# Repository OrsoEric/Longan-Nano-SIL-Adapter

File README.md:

# Longan-Nano-SIL-Adapter
SIL Adapter for the Longan Nano evaluation board for the GD32VF103. Allows vertical mounting for the board. Includes RS485 communication with 3.5mm Audio Jacks.

**Connector Pinout**  

**Schematics**  

**Routing**  

**Gerber**  

**BOM**
*Part* 	*Value*  
CB-COM-1 	1u  
CF-COM-1 	100n  
CF-COM-2 	100n  
CON-COM-1 	JACK_SMD_3MM5  
CON-COM-2 	JACK_SMD_3MM5  
CON-UC-1 	2X2.54mm Male  
CON-UC-2 	8X2.54mm Male  
CON-UC-3 	8X2.54mm Male  
CP-UC-1 	100u  
IC-COM-1 	SN75176  
IC-UC-1 	LONGAN-NANO  
LF1-COM-1 	BEAD 500mA  
RD-COM-1 	720  
RS-COM-2 	10  
RS-COM-3 	10  
RS-UC-1 	4X1K  
RT-COM-1 	120  
RU-COM-1 	720

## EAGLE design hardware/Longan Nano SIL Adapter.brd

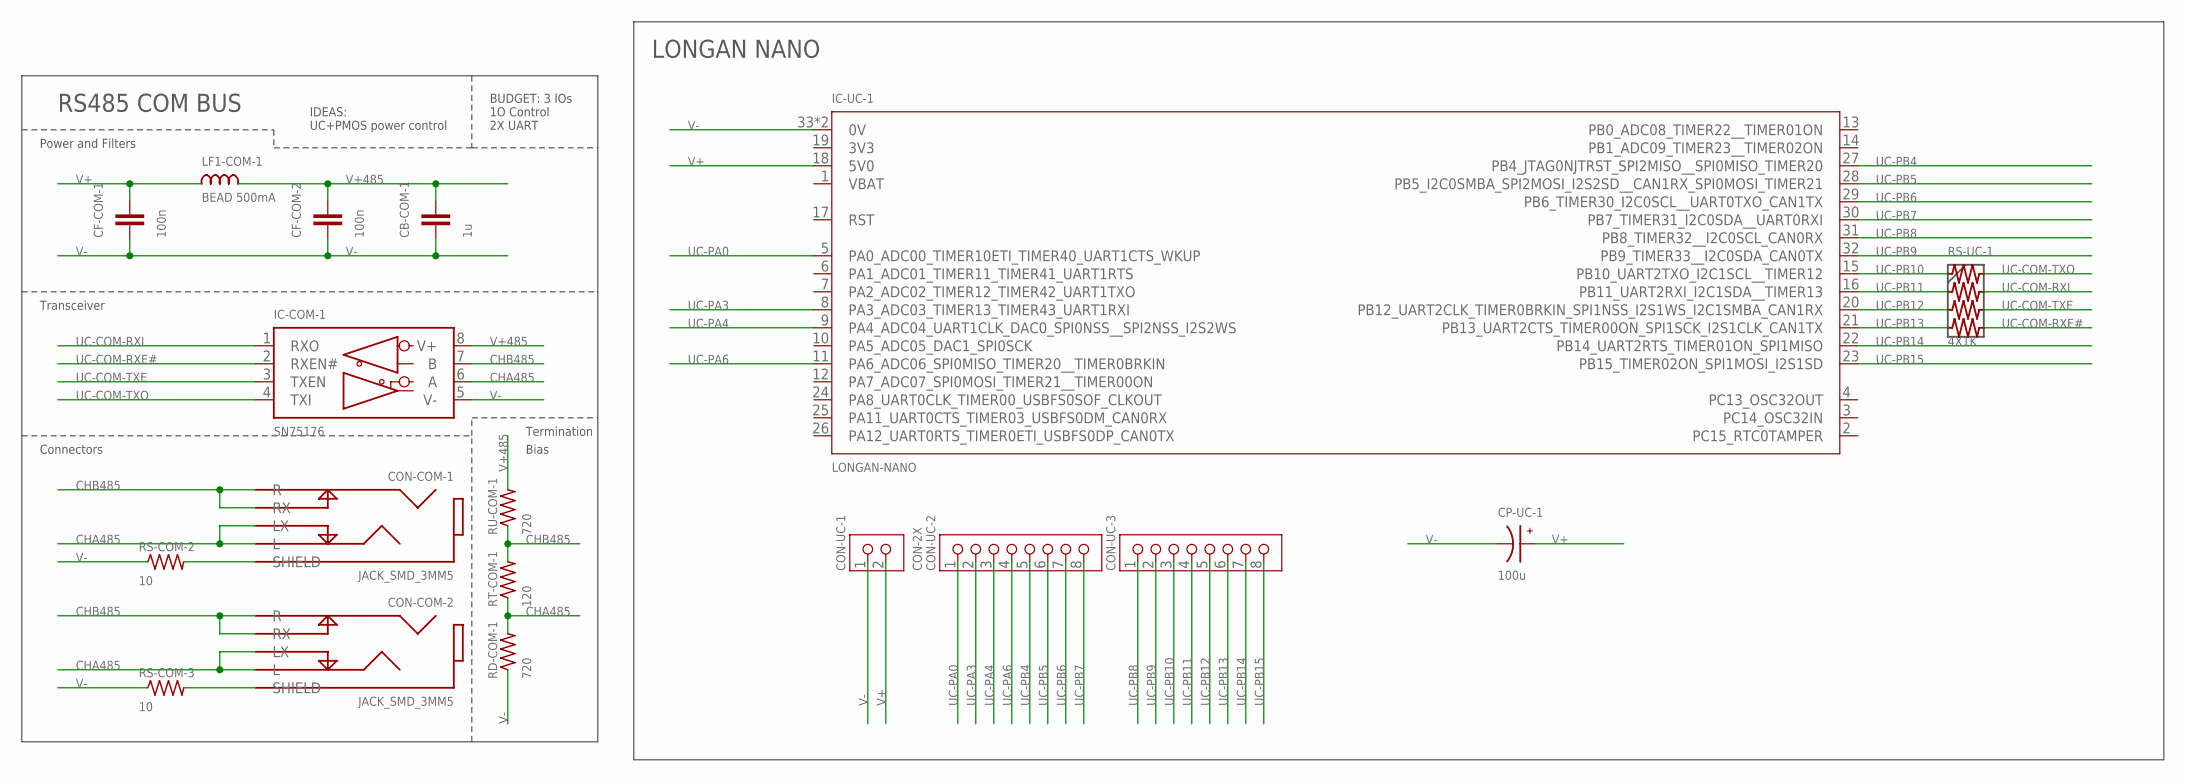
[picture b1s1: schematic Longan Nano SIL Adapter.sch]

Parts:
CB-COM-1: 1u; SMD-M2012
CF-COM-1, CF-COM-2: 100n; SMD-M2012
CON-COM-1, CON-COM-2: JACK_SMD_3MM5
CON-UC-1: CON-2X; TH-2X2.54
CON-UC-2, CON-UC-3: CON-8X; TH-8X2.54
CP-UC-1: 100u; TH-BARREL-2M54-6M0
IC-COM-1: SN75176; DIL08
IC-UC-1: LONGAN-NANO
LF1-COM-1: BEAD 500mA; SMD-M2012
RD-COM-1: 720; SMD-M2012
RS-COM-2, RS-COM-3: 10; SMD-M2012
RS-UC-1: 4X1K; SMD-M2012-X4
RT-COM-1: 120; TH-LINE-2M54-3M0
RU-COM-1: 720; SMD-M2012

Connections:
3V3: IC-UC-1.19 (3V3)
CHA485: CON-COM-1.L, CON-COM-1.LX, CON-COM-2.L, CON-COM-2.LX, IC-COM-1.6 (A), RD-COM-1.2, RT-COM-1.P$1 (1)
CHB485: CON-COM-1.R, CON-COM-1.RX, CON-COM-2.R, CON-COM-2.RX, IC-COM-1.7 (B), RT-COM-1.P$2 (2), RU-COM-1.1
unnamed: CON-COM-1.SHIELD, RS-COM-2.2
unnamed: CON-COM-2.SHIELD, RS-COM-3.2
UC-COM-RXE#: IC-COM-1.2 (RXEN#), RS-UC-1.4B
UC-COM-RXI: IC-COM-1.1 (RXO), RS-UC-1.2B
UC-COM-TXE: IC-COM-1.3 (TXEN), RS-UC-1.3B
UC-COM-TXO: IC-COM-1.4 (TXI), RS-UC-1.1B
UC-PA0: CON-UC-2.1, IC-UC-1.5 (PA0_ADC00_TIMER10ETI_TIMER40_UART1CTS_W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)
UC-PA3: CON-UC-2.2, IC-UC-1.8 (PA3_ADC03_TIMER13_TIMER43_UART1RXI)
UC-PA4: CON-UC-2.3, IC-UC-1.9 (PA4_ADC04_UART1CLK_DAC0_SPI0NSS__SPI2NS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)
UC-PA6: CON-UC-2.4, IC-UC-1.11 (PA6_ADC06_SPI0MISO_TIMER20__TIMER0BRKIN)
UC-PB4: CON-UC-2.5, IC-UC-1.27 (PB4_JTAG0NJTRST_SPI2MISO__SPI0MISO_TIME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)
UC-PB5: CON-UC-2.6, IC-UC-1.28 (PB5_I2C0SMBA_SPI2MOSI_I2S2SD__CAN1RX_SP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)
UC-PB6: CON-UC-2.7, IC-UC-1.29 (PB6_TIMER30_I2C0SCL__UART0TXO_CAN1TX)
UC-PB7: CON-UC-2.8, IC-UC-1.30 (PB7_TIMER31_I2C0SDA__UART0RXI)
UC-PB8: CON-UC-3.1, IC-UC-1.31 (PB8_TIMER32__I2C0SCL_CAN0RX)
UC-PB9: CON-UC-3.2, IC-UC-1.32 (PB9_TIMER33__I2C0SDA_CAN0TX)
UC-PB10: CON-UC-3.3, IC-UC-1.15 (PB10_UART2TXO_I2C1SCL__TIMER12), RS-UC-1.1A
UC-PB11: CON-UC-3.4, IC-UC-1.16 (PB11_UART2RXI_I2C1SDA__TIMER13), RS-UC-1.2A
UC-PB12: CON-UC-3.5, IC-UC-1.20 (PB12_UART2CLK_TIMER0BRKIN_SPI1NSS_I2S1W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), RS-UC-1.3A
UC-PB13: CON-UC-3.6, IC-UC-1.21 (PB13_UART2CTS_TIMER00ON_SPI1SCK_I2S1CLK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), RS-UC-1.4A
UC-PB14: CON-UC-3.7, IC-UC-1.22 (PB14_UART2RTS_TIMER01ON_SPI1MISO)
UC-PB15: CON-UC-3.8, IC-UC-1.23 (PB15_TIMER02ON_SPI1MOSI_I2S1SD)
V+: CF-COM-1.2, CON-UC-1.2, CP-UC-1.+, IC-UC-1.18 (5V0), LF1-COM-1.1
V+485: CB-COM-1.2, CF-COM-2.2, IC-COM-1.8 (V+), LF1-COM-1.2, RU-COM-1.2
V-: CB-COM-1.1, CF-COM-1.1, CF-COM-2.1, CON-UC-1.1, CP-UC-1.-, IC-COM-1.5 (V-), IC-UC-1.33 (0V), IC-UC-1.34 (0V), RD-COM-1.1, RS-COM-2.1, RS-COM-3.1
VBAT: IC-UC-1.1 (VBAT)

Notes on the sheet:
RS485 COM BUS
Power and Filters
Transceiver
Connectors
Termination
Bias
BUDGET: 3 IOs 1O Control 2X UART
IDEAS: UC+PMOS power control
LONGAN NANO

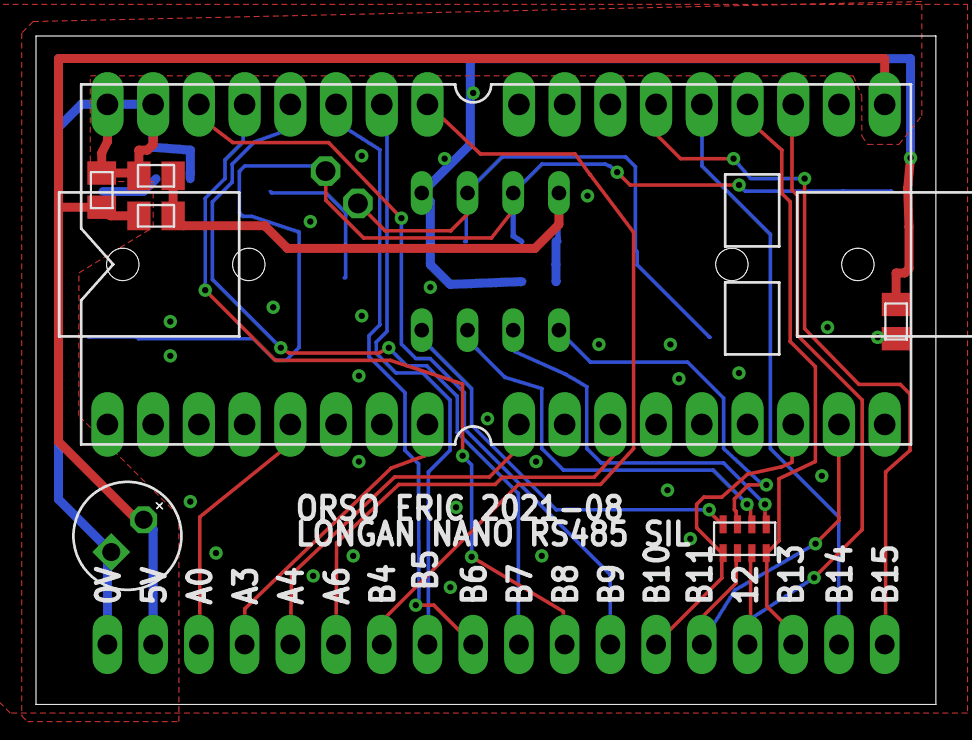
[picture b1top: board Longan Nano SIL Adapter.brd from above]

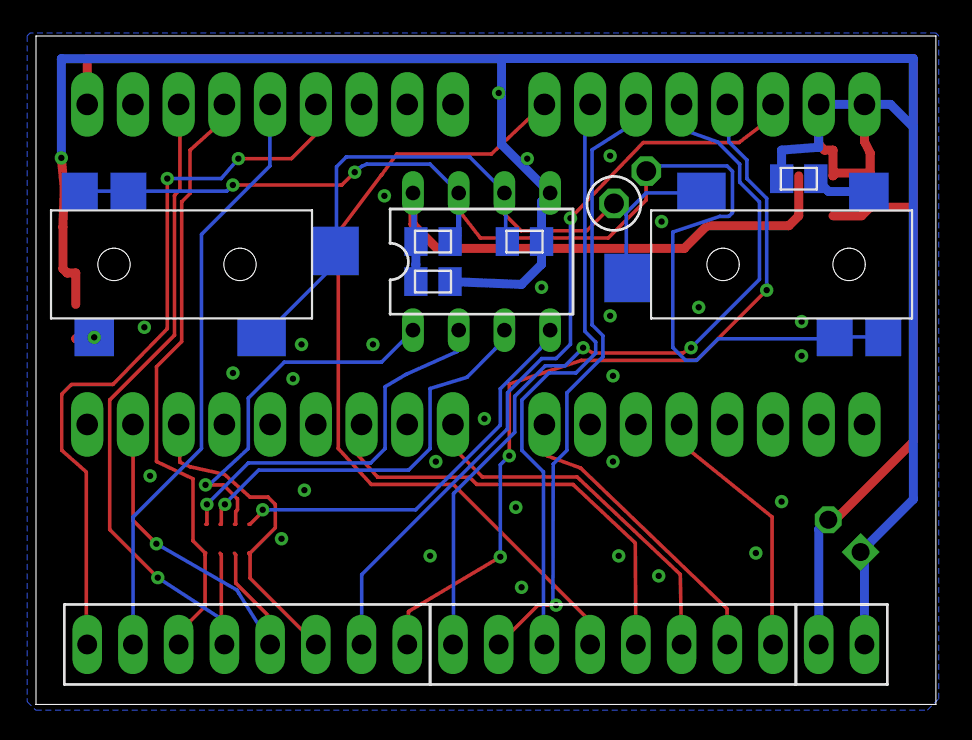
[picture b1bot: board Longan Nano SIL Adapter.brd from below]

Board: 2 copper layers, 50.0 x 37.1 mm, 20 parts (11 on the bottom side), 27 nets.

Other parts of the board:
U$1: SIGNATURE_ADROBOT_SMALL
U$2: SIGNATURE_ORANGEBOT_SMALL

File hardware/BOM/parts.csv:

Part;Value;Device;Package;Description;MF;MPN;OC_FARNELL;OC_NEWARK
CB-COM-1;1u;C-M2012;SMD-M2012;Capacitor;;;;
CF-COM-1;100n;C-M2012;SMD-M2012;Capacitor;;;;
CF-COM-2;100n;C-M2012;SMD-M2012;Capacitor;;;;
CON-COM-1;JACK_SMD_3MM5;JACK_SMD_3MM5;JACK_SMD_3MM5;Jack 3.5mm;;;;
CON-COM-2;JACK_SMD_3MM5;JACK_SMD_3MM5;JACK_SMD_3MM5;Jack 3.5mm;;;;
CON-UC-1;2X2.54mm Male;CON-2X;TH-2X2.54;Generic connector two pins;;;;
CON-UC-2;8X2.54mm Male;CON-8X;TH-8X2.54;PIN HEADER;;;;
CON-UC-3;8X2.54mm Male;CON-8X;TH-8X2.54;PIN HEADER;;;;
CP-UC-1;100u;C+-TH2.54-6.0;TH-BARREL-2M54-6M0;Polarized Capacitor;;;;
IC-COM-1;SN75176;RS485;DIL08;RS485 TRANSEIVER;;MAX481CPA+;unknown;99K3445
IC-UC-1;LONGAN-NANO;LONGAN-NANO;LONGAN-NANO;Longan Nano;;;;
LF1-COM-1;BEAD 500mA;L-M2012;SMD-M2012;Inductor;;;;
RD-COM-1;720;R-M2012;SMD-M2012;Resistor;;;;
RS-COM-2;10;R-M2012;SMD-M2012;Resistor;;;;
RS-COM-3;10;R-M2012;SMD-M2012;Resistor;;;;
RS-UC-1;4X1K;RX4-M2012-X4;SMD-M2012-X4;Four Resistor;;;;
RT-COM-1;120;R-V2.54-3.0;TH-LINE-2M54-3M0;Resistor;;;;
RU-COM-1;720;R-M2012;SMD-M2012;Resistor;;;;

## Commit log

2021-08-15 Uploads Eagle Project
2021-08-15 adds connector pinout to readme
2021-08-17 adds image of full schematics
2021-08-17 adds Gerber Files
2021-08-17 adds image of gerber production files
2021-08-17 final schematics and routing
2021-08-17 updates readme with final schematics, routing and gerber.
2021-08-17 adds BOM
2021-08-22 updates production schematic, pcb and gerber. adds part list.
